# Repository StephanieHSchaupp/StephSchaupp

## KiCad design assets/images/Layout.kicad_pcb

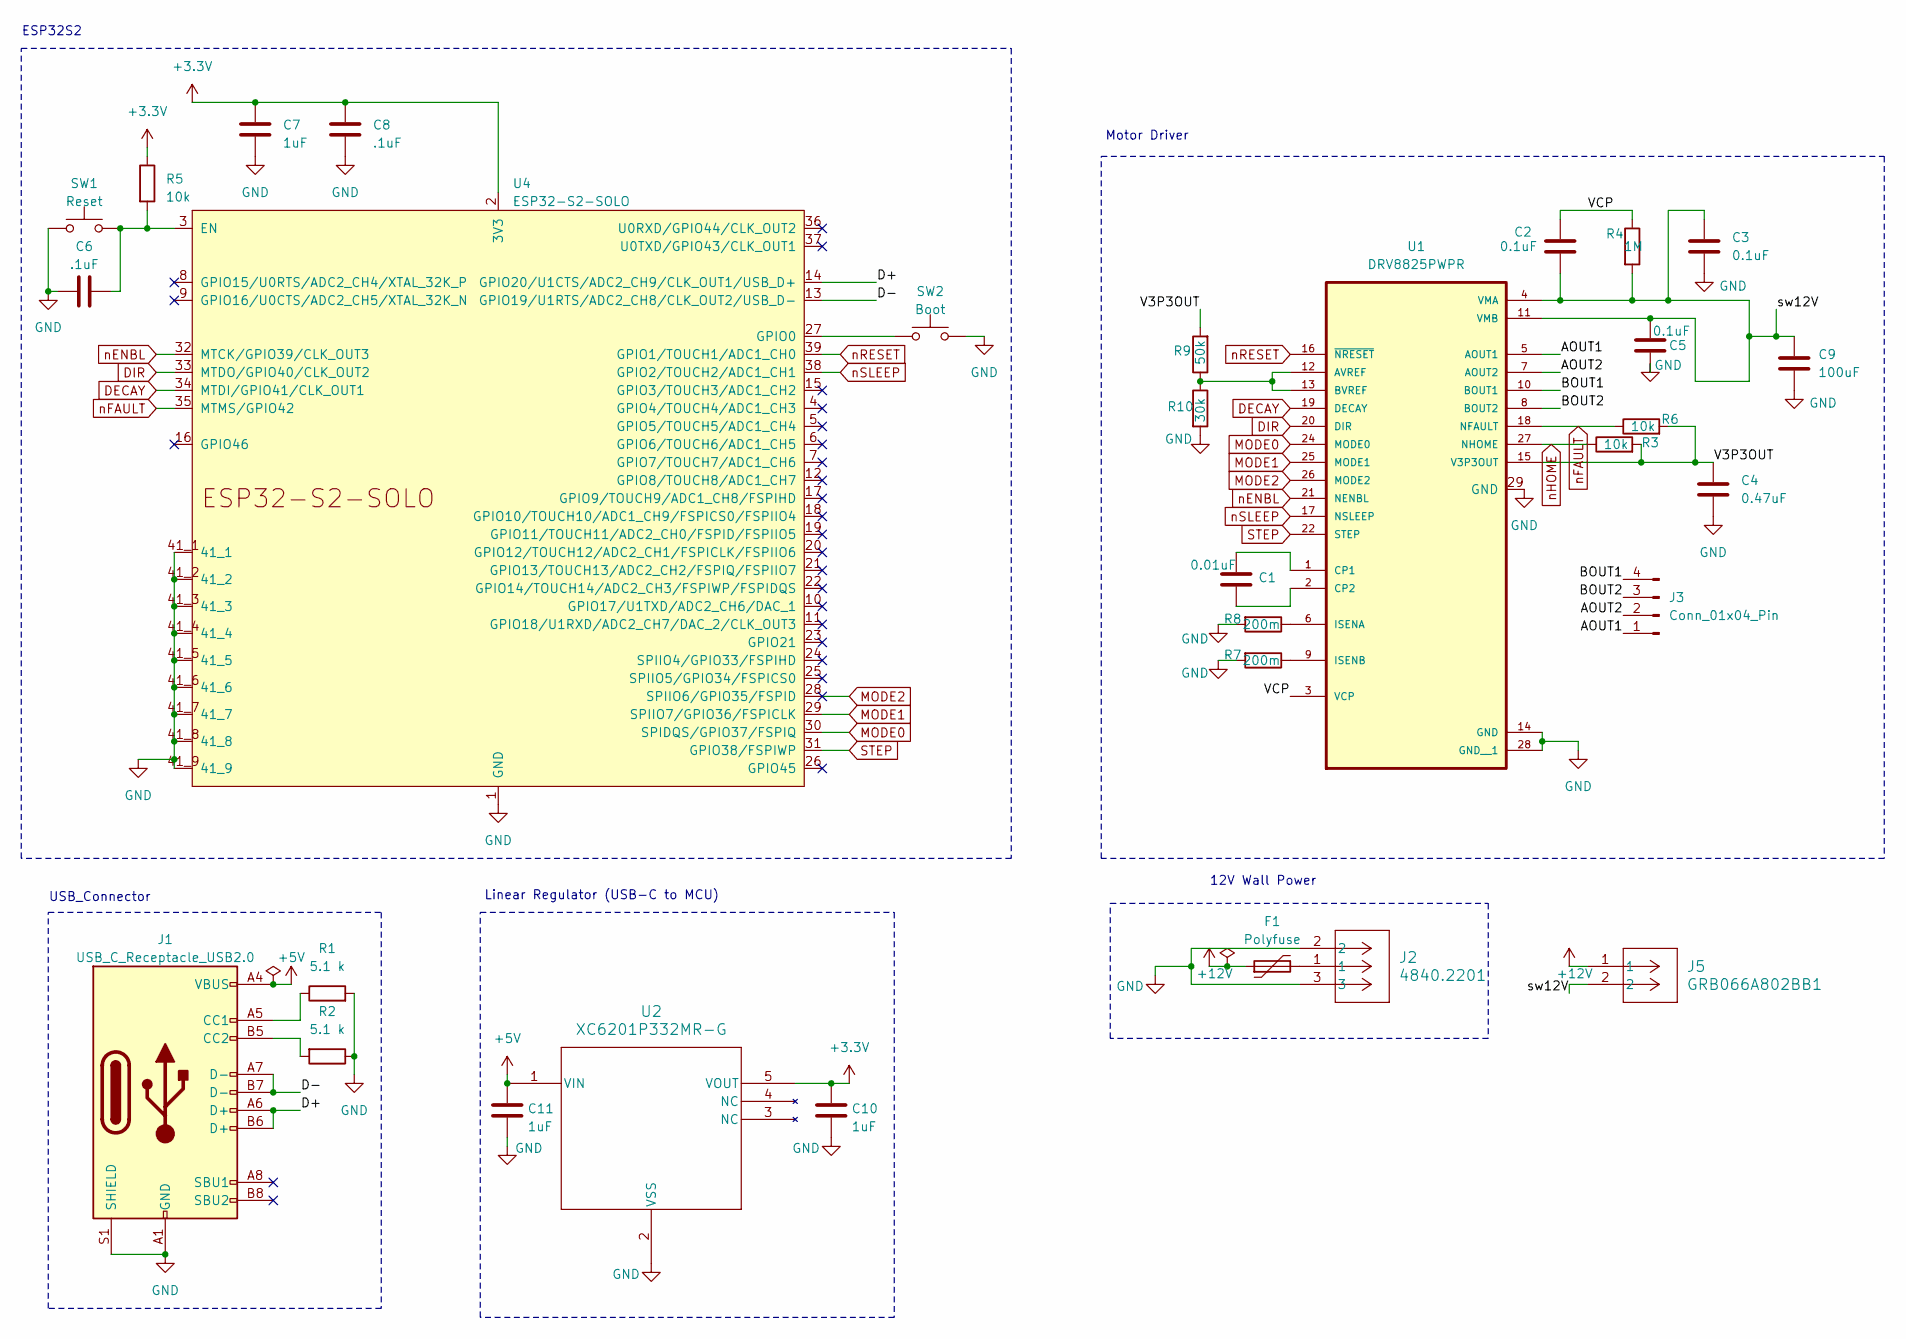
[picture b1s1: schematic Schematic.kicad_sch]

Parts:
C1: 0.01uF; C_0805_2012Metric_Pad1.18x1.45mm_HandSolder
C2, C3, C5: 0.1uF; C_0805_2012Metric_Pad1.18x1.45mm_HandSolder
C4: 0.47uF; C_0805_2012Metric_Pad1.18x1.45mm_HandSolder
C6, C8: .1uF; C_0805_2012Metric_Pad1.18x1.45mm_HandSolder
C7, C10, C11: 1uF; C_0805_2012Metric_Pad1.18x1.45mm_HandSolder
C9: 100uF; C_0805_2012Metric_Pad1.18x1.45mm_HandSolder
F1: Polyfuse; Fuse_1812_4532Metric_Pad1.30x3.40mm_HandSolder
J1: USB_C_Receptacle_USB2.0; USB_C_Receptacle_GCT_USB4105-xx-A_16P_TopMnt_Horizontal
J2: 4840.2201; CONN_4840.2201_SCH
J3: Conn_01x04_Pin; JST_PH_B4B-PH-K_1x04_P2.00mm_Vertical
J5: GRB066A802BB1; CONN2_GRB066A802BB1_CYP
R1, R2: 5.1 k; R_0805_2012Metric_Pad1.20x1.40mm_HandSolder
R3, R5, R6: 10k; R_0805_2012Metric_Pad1.20x1.40mm_HandSolder
R4: 1M; R_0805_2012Metric_Pad1.20x1.40mm_HandSolder
R7, R8: 200m; R_0805_2012Metric_Pad1.20x1.40mm_HandSolder
R9: 50k; R_0805_2012Metric_Pad1.20x1.40mm_HandSolder
R10: 30k; R_0805_2012Metric_Pad1.20x1.40mm_HandSolder
SW1: Reset; SW_SKRPACE010_AAL
SW2: Boot; SW_SKRPACE010_AAL
U1: DRV8825PWPR; IC_TPS61196PWPRQ1
U2: XC6201P332MR-G; XC6201_SOT-25_TOR
U4: ESP32-S2-SOLO; XCVR_ESP32-S2-SOLO-N4

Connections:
+3.3V: C7.1, C8.1, C10.2, R5.1, U2.5 (VOUT), U4.2 (3V3)
+5V: C11.2, J1.A4 (VBUS), J1.A9 (VBUS), J1.B4 (VBUS), J1.B9 (VBUS), U2.1 (VIN)
+12V: F1.1, J5.1
/AOUT1: J3.1, U1.5 (AOUT1)
/AOUT2: J3.2, U1.7 (AOUT2)
/BOUT1: J3.4, U1.10 (BOUT1)
/BOUT2: J3.3, U1.8 (BOUT2)
/D+: J1.A6 (D+), J1.B6 (D+), U4.14 (GPIO20/U1CTS/ADC2_CH9/CLK_OUT1/USB_D+)
/D-: J1.A7 (D-), J1.B7 (D-), U4.13 (GPIO19/U1RTS/ADC2_CH8/CLK_OUT2/USB_D-)
/V3P3OUT: C4.2, R3.2, R6.2, R9.2, U1.15 (V3P3OUT)
/VCP: C2.1, R4.1, U1.3 (VCP)
/sw12V: C2.2, C3.1, C5.1, C9.1, J5.2, R4.2, U1.4 (VMA), U1.11 (VMB)
DECAY: U1.19 (DECAY), U4.34 (MTDI/GPIO41/CLK_OUT1)
DIR: U1.20 (DIR), U4.33 (MTDO/GPIO40/CLK_OUT2)
GND: C3.2, C4.1, C5.2, C6.1, C7.2, C8.2, C9.2, C10.1, C11.1, J1.A1 (GND), J1.A12 (GND), J1.B1 (GND), J1.B12 (GND), J1.S1 (SHIELD), J2.2, J2.3, R1.2, R2.1, R7.2, R8.2, R10.2, SW1.1, SW2.2, U1.14 (GND), U1.28 (GND__1), U1.29 (GND), U2.2 (VSS), U4.1 (GND), U4.40 (GND), U4.41 (GND), U4.41_1, U4.41_2, U4.41_3, U4.41_4, U4.41_5, U4.41_6, U4.41_7, U4.41_8, U4.41_9
MODE0: U1.24 (MODE0), U4.30 (SPIDQS/GPIO37/FSPIQ)
MODE1: U1.25 (MODE1), U4.29 (SPIIO7/GPIO36/FSPICLK)
MODE2: U1.26 (MODE2), U4.28 (SPIIO6/GPIO35/FSPID)
unnamed: F1.2, J2.1
unnamed: J1.A5 (CC1), R1.1
unnamed: J1.B5 (CC2), R2.2
unnamed: R9.1, R10.1, U1.12 (AVREF), U1.13 (BVREF)
unnamed: C1.1, U1.1 (CP1)
unnamed: C1.2, U1.2 (CP2)
unnamed: R8.1, U1.6 (ISENA)
unnamed: R7.1, U1.9 (ISENB)
unnamed: C6.2, R5.2, SW1.2, U4.3 (EN)
unnamed: SW2.1, U4.27 (GPIO0)
STEP: U1.22 (STEP), U4.31 (GPIO38/FSPIWP)
nENBL: U1.21 (NENBL), U4.32 (MTCK/GPIO39/CLK_OUT3)
nFAULT: R6.1, U1.18 (NFAULT), U4.35 (MTMS/GPIO42)
nHOME: R3.1, U1.27 (NHOME)
nRESET: U1.16 (~NRESET), U4.39 (GPIO1/TOUCH1/ADC1_CH0)
nSLEEP: U1.17 (NSLEEP), U4.38 (GPIO2/TOUCH2/ADC1_CH1)

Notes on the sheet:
USB_Connector
ESP32S2
12V Wall Power
Linear Regulator (USB-C to MCU)
Motor Driver

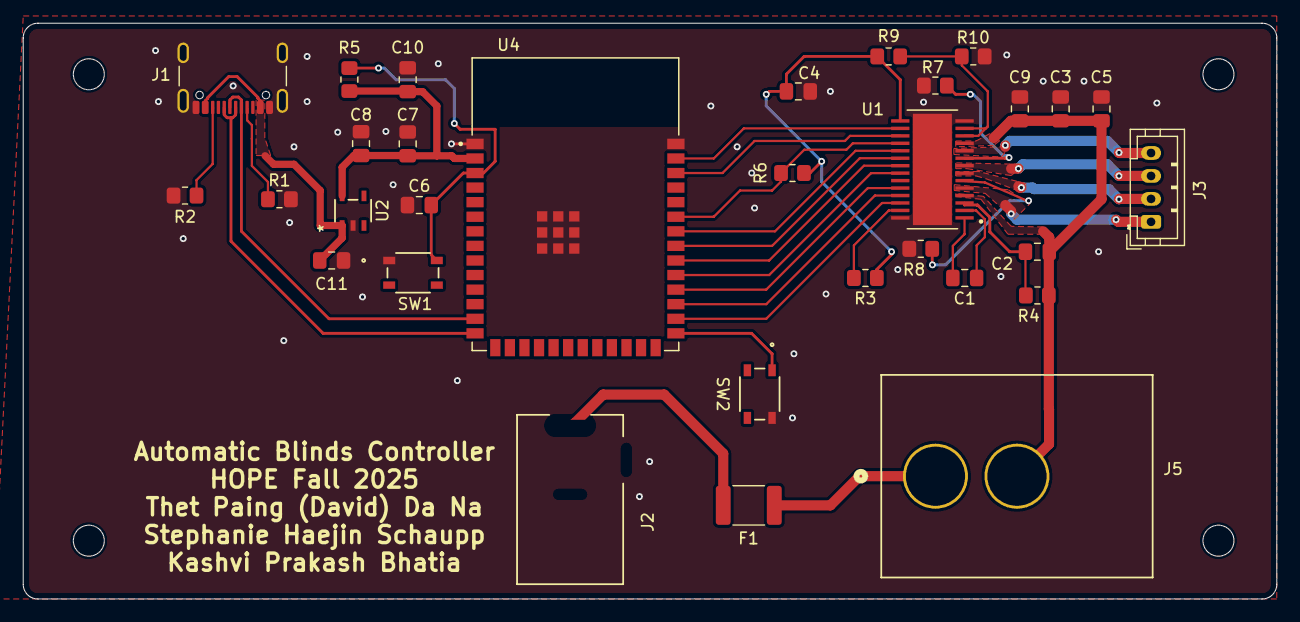
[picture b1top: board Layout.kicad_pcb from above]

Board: 2 copper layers, 109.2 x 50.2 mm, 31 parts (0 on the bottom side), 34 nets.

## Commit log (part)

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2025-10-20 Rename Rectifier.ong.png to Rectifier.png
2025-12-27 Update links for PCB schematic and layout images
2025-12-27 Update project links and fix text duplication
    Removed duplicate links and corrected text in project description.
